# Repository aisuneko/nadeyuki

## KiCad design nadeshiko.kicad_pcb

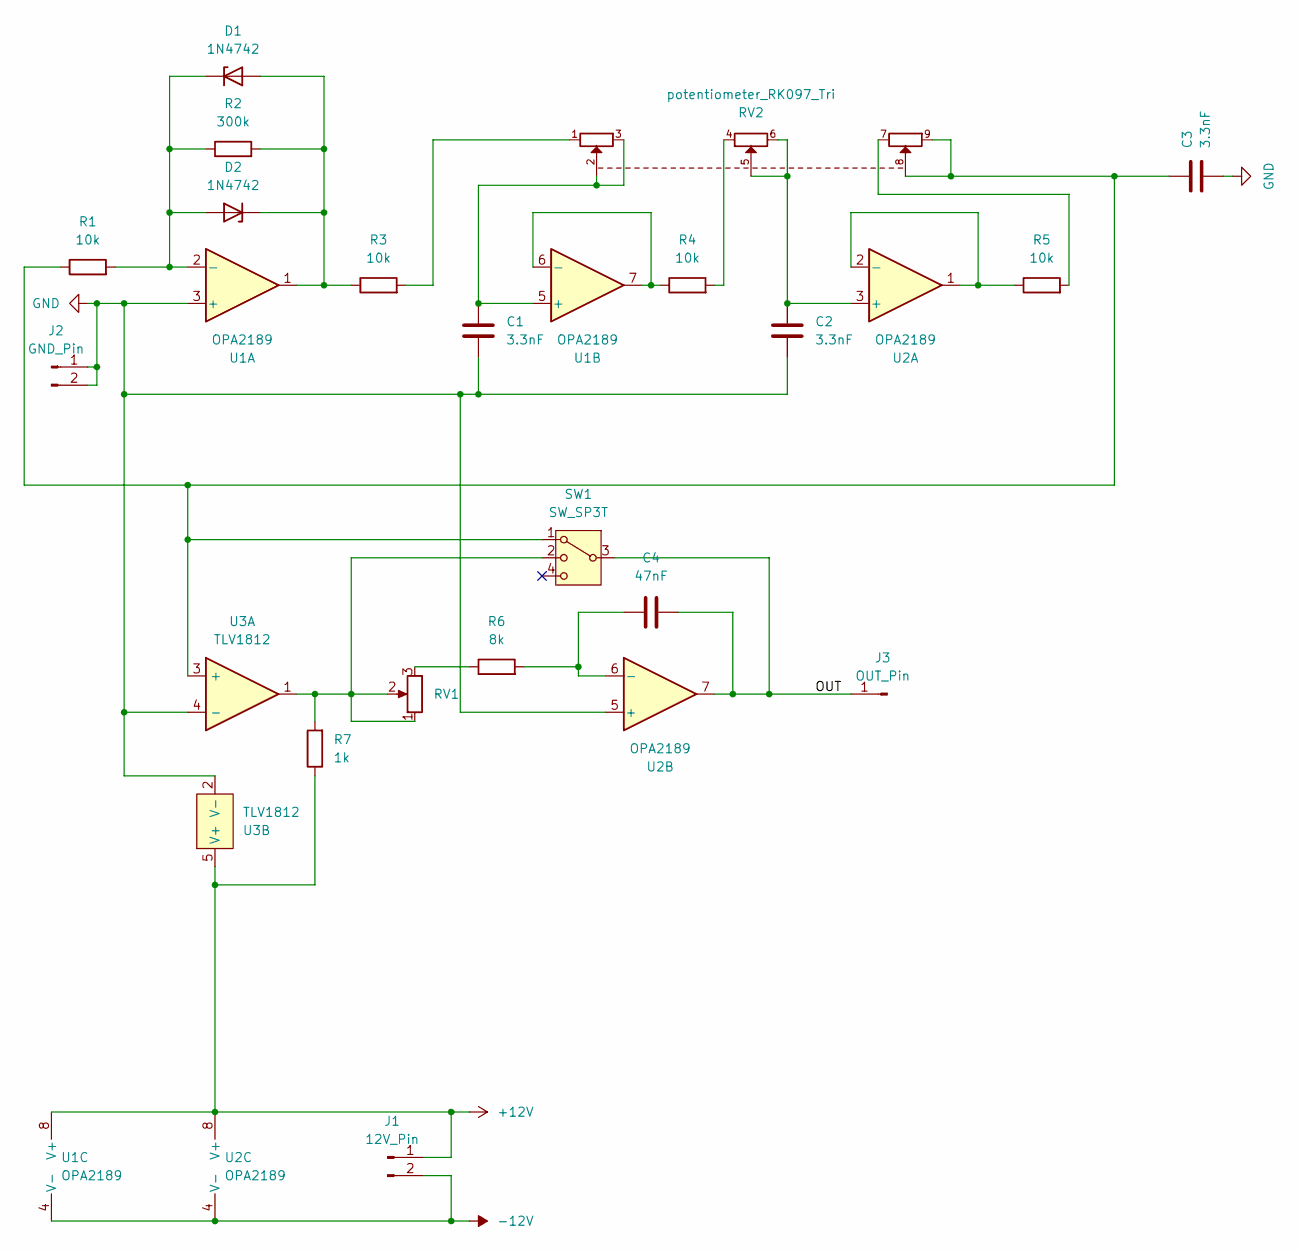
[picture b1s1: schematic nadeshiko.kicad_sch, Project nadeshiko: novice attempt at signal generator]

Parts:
C1, C2, C3: 3.3nF; C_0805_2012Metric_Pad1.18x1.45mm_HandSolder
C4: 47nF; C_0805_2012Metric_Pad1.18x1.45mm_HandSolder
D1, D2: 1N4742; D_DO-41_SOD81_P10.16mm_Horizontal
J1: 12V_Pin; PinHeader_1x02_P2.54mm_Vertical
J2: GND_Pin; PinHeader_1x02_P2.54mm_Vertical
J3: OUT_Pin; PinHeader_1x01_P2.54mm_Vertical
R1, R3, R4, R5: 10k; R_0805_2012Metric_Pad1.20x1.40mm_HandSolder
R2: 300k; R_0805_2012Metric_Pad1.20x1.40mm_HandSolder
R6: 8k; R_0805_2012Metric_Pad1.20x1.40mm_HandSolder
R7: 1k; R_0805_2012Metric_Pad1.20x1.40mm_HandSolder
RV1: R_Potentiometer; Potentiometer_Bourns_3296W_Vertical
RV2: potentiometer_RK097_Tri
SW1: SW_SP3T; SW_SP3T_PCM13
U1, U2: OPA2189; SOIC-8_3.9x4.9mm_P1.27mm
U3: TLV1812; SOT-23-5_HandSoldering; Part Number TLV171IDVBR

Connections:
+12V: J1.1, R7.1, U1.8 (V+), U2.8 (V+), U3.5 (V+)
-12V: J1.2, U1.4 (V-), U2.4 (V-)
/OUT: C4.2, J3.1, SW1.3, U2.7
GND: C1.2, C2.2, C3.2, J2.1, J2.2, U1.3 (+), U2.5 (+), U3.2 (V-), U3.4 (-)
unnamed: D1.2 (A), D2.1 (K), R2.2, R3.1, U1.1
unnamed: D1.1 (K), D2.2 (A), R1.2, R2.1, U1.2 (-)
unnamed: R3.2, RV2.1
unnamed: R4.2, RV2.4
unnamed: R5.2, RV2.7
unnamed: R6.1, RV1.3
unnamed: R7.2, RV1.1, RV1.2, SW1.2, U3.1
unnamed: C1.1, RV2.2, RV2.3, U1.5 (+)
unnamed: R4.1, U1.6 (-), U1.7
unnamed: C2.1, RV2.5, RV2.6, U2.3 (+)
unnamed: R5.1, U2.1, U2.2 (-)
unnamed: C4.1, R6.2, U2.6 (-)
unnamed: C3.1, R1.1, RV2.8, RV2.9, SW1.1, U3.3 (+)

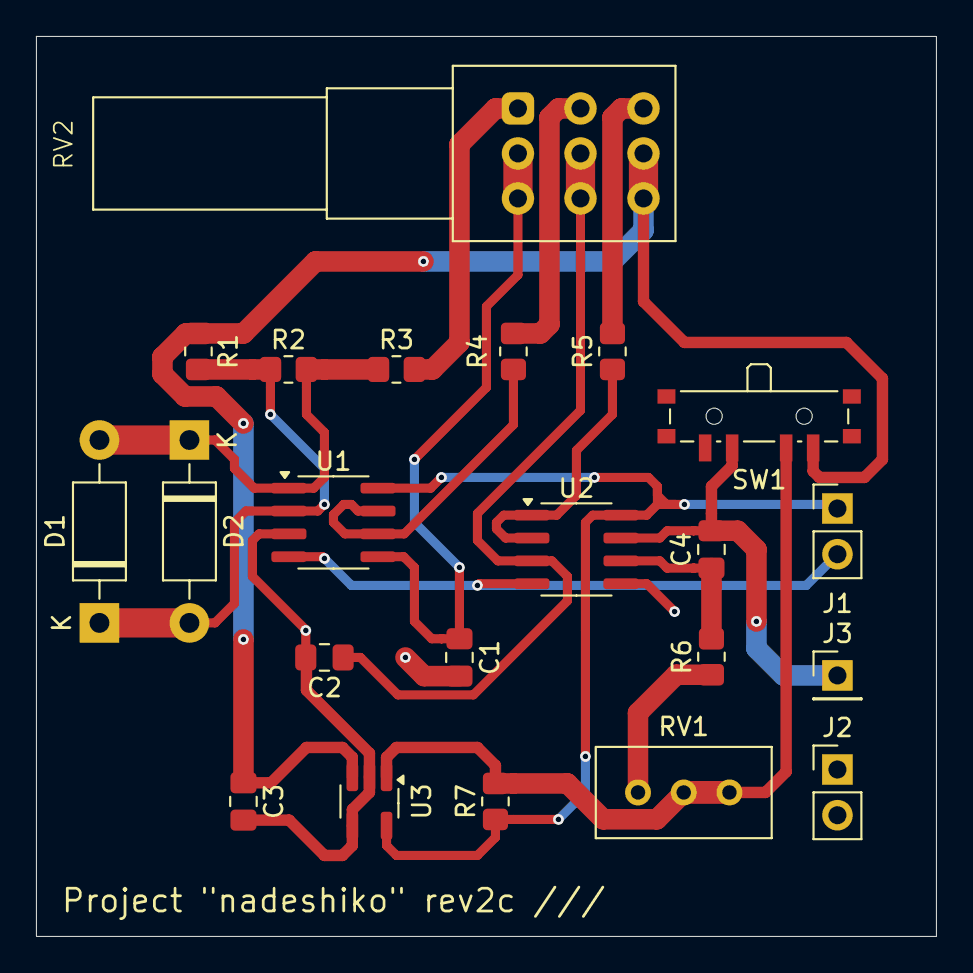
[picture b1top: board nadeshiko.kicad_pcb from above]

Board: 2 copper layers, 50.0 x 50.0 mm, 22 parts (0 on the bottom side), 17 nets.

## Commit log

2024-11-14 Schema v2
2024-11-14 Schema v2a & custom footprint
2024-11-14 fix Schema
2024-11-16 rev2c
2024-11-19 finalize rev2c
2024-12-27 finalize
2024-12-27 update dirs
2024-12-27 add yukiyuna
